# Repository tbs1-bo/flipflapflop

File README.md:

# flipflapflop
Steuerung einer Flipdot-Zielanzeige mit verschiedenen Mikrocontrollern.

Die Dokumentation befindet sich unter https://tbs1-bo.github.io/flipflapflop/

Die Demos lassen sich ganz ohne Installation direkt im Browser auf einer
virtuellen Flipdot-Anzeige ausprobieren:
https://tbs1-bo.github.io/flipflapflop/webdemo/ (Quelle: [webdemo/](webdemo/)).
  
Ein ähnliches Projekt zur Ansteuerung von LED-Anzeigen ist unter
[BoLED](https://github.com/tbs1-bo/BoLED) zu finden.

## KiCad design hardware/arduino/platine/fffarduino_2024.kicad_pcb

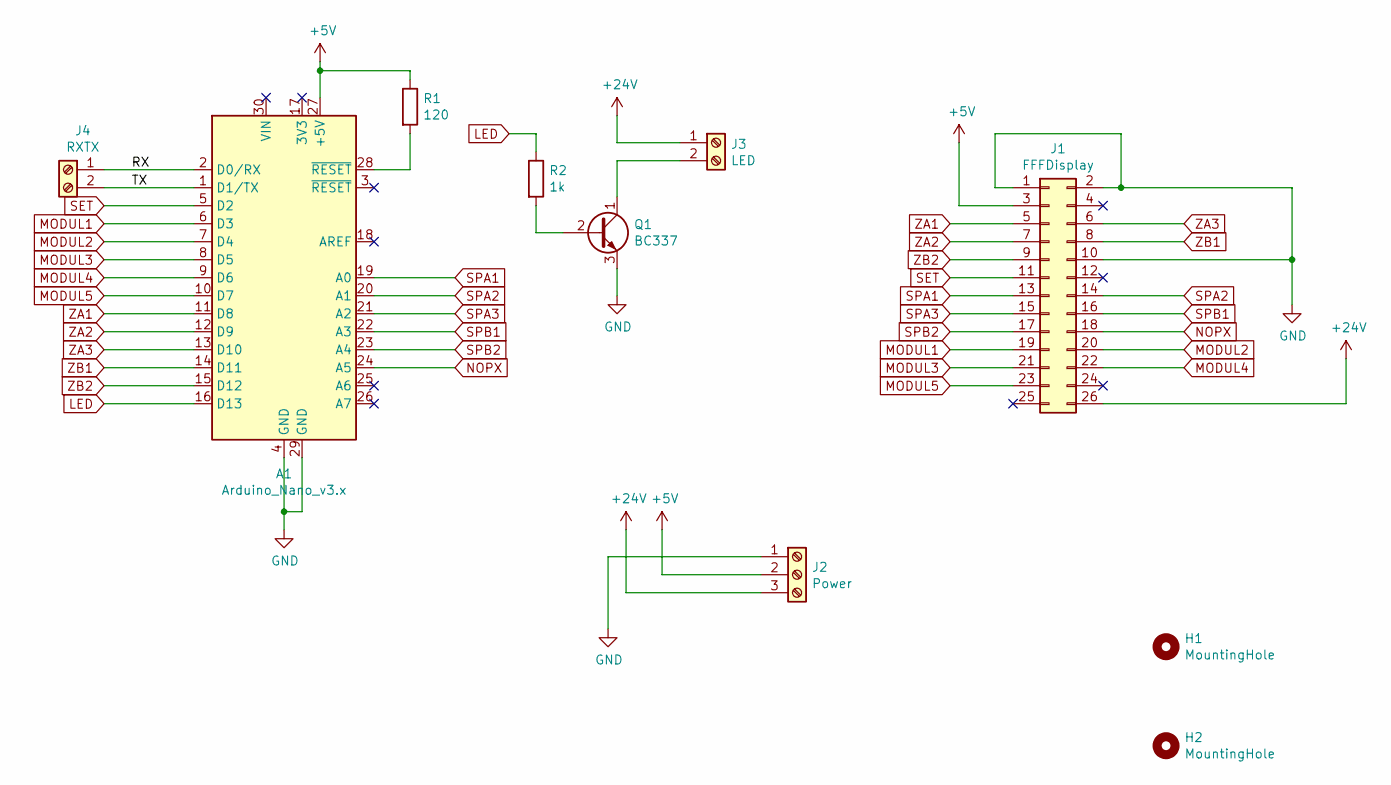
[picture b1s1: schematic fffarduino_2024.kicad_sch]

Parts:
A1: Arduino_Nano_v3.x; Arduino_Nano
H1: MountingHole; MountingHole_3.2mm_M3
H2: MountingHole; MountingHole_3mm
J1: FFFDisplay; PinHeader_2x13_P2.54mm_Horizontal
J2: Power; PhoenixContact_MSTBVA_2,5_3-G-5,08_1x03_P5.08mm_Vertical
J3: LED; PhoenixContact_MSTBVA_2,5_2-G-5,08_1x02_P5.08mm_Vertical
J4: RXTX; PinHeader_1x02_P2.54mm_Horizontal
Q1: BC337; TO-92_Wide
R1: 120; R_Axial_DIN0204_L3.6mm_D1.6mm_P2.54mm_Vertical
R2: 1k; R_Axial_DIN0207_L6.3mm_D2.5mm_P10.16mm_Horizontal

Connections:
+5V: A1.27 (+5V), J1.3, J2.2, R1.1
+24V: J1.26, J2.3, J3.1
/RX: A1.2 (D0/RX), J4.1
/TX: A1.1 (D1/TX), J4.2
GND: A1.4 (GND), A1.29 (GND), J1.1, J1.2, J1.10, J2.1, Q1.3 (E)
LED: A1.16 (D13), R2.1
MODUL1: A1.6 (D3), J1.19
MODUL2: A1.7 (D4), J1.20
MODUL3: A1.8 (D5), J1.21
MODUL4: A1.9 (D6), J1.22
MODUL5: A1.10 (D7), J1.23
NOPX: A1.24 (A5), J1.18
unnamed: A1.28 (~RESET), R1.2
unnamed: J3.2, Q1.1 (C)
unnamed: Q1.2 (B), R2.2
SET: A1.5 (D2), J1.11
SPA1: A1.19 (A0), J1.13
SPA2: A1.20 (A1), J1.14
SPA3: A1.21 (A2), J1.15
SPB1: A1.22 (A3), J1.16
SPB2: A1.23 (A4), J1.17
ZA1: A1.11 (D8), J1.5
ZA2: A1.12 (D9), J1.7
ZA3: A1.13 (D10), J1.6
ZB1: A1.14 (D11), J1.8
ZB2: A1.15 (D12), J1.9

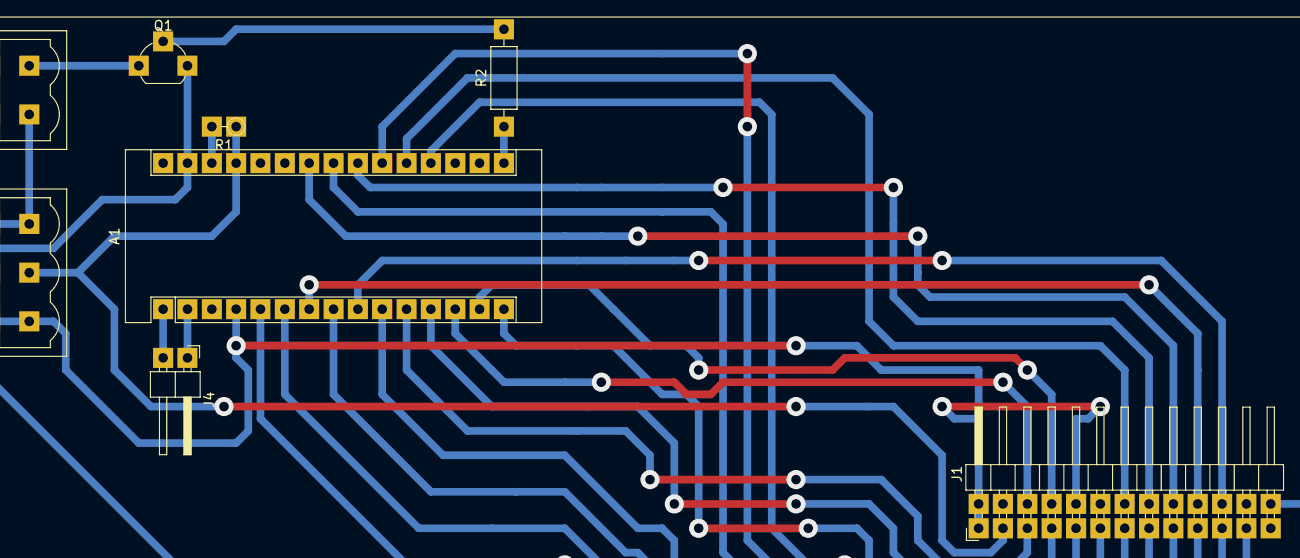
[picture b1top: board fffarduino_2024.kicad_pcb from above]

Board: 2 copper layers, 10 parts (0 on the bottom side), 26 nets.

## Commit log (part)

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2019-11-12 changed default topic name
2019-11-15 added make target for config file.
2020-05-09 gamejamdo
2020-05-09 gamejamdo
    gamejamdo
    gamejamdo
    gamejamdo
    gamejamdo
    gamejamdo
    gamejamdo
2020-05-09 lt19: removed special handling for ctf.
2020-05-10 typo
2020-05-11 gamejamdo: moved into module.
2020-05-11 formating
2020-05-11 making venv in parent.
2020-05-11 using release instead of git.
2020-05-11 removed ii.
2020-05-11 version configurable
2020-05-30 Beschreibung ergänzt.
2020-06-02 bf verlinkt
2020-07-24 doc: add link to handle auto reset.
2020-10-08 removed special handling for lt19
2020-10-08 index route removed
2020-10-08 parameter checking
2020-10-08 added test
2020-10-08 reordering imports
2020-10-08 formatting
2020-10-09 add: target for web
2020-10-09 added pygame requirement for arch
2020-10-09 added get_display
2020-10-09 whole image can be sent to display
    new route /page with
2020-10-09 second version for web interface.
    based on hug.
2020-10-10 added index page
2020-10-10 removed hug base web interface.
    in favor of flask.
2020-10-10 cofigurable webserver host.
2020-10-11 iframe of the video can be configured.
2020-10-12 display dimension shown
2020-10-12 add: test for plasma demo
2020-10-18 format
2020-10-18 GET route /page returns display content
2020-10-18 iframe in website replaced by link.
2020-10-18 removed small method set_buffer
2020-10-18 add 'x' for ignoring positions in page route
2020-10-18 removed unused import
2020-10-19 lni ressources
2020-10-19 add examples for the terminal.
2020-10-19 areas for the display
2020-10-19 added todo
2020-10-28 f strings removed
2020-10-28 add reverse_tunnel target
2020-10-28 added plasmademo remote test
2020-10-28 LNI20 startscreen
2020-10-28 aufgaben
2020-11-07 benchmarking the display
2020-11-13 minor change
2020-11-14 added feedback info.
2020-11-14 merges changes from branch lni_stat.
2020-11-14 lni20: demo
2021-10-11 gitlabci: add pip3 dependency
2022-10-30 adding pyproject file
2023-12-06 added flask
2023-12-06 font parameter no longer needed.
2023-12-06 added route to display text
2023-12-06 rm live image
2023-12-06 fetch use protocol
2023-12-06 request no longer form data
2023-12-06 rm unused
2023-12-21 pylint v3.0.3
2023-12-21 ignore cached files
2023-12-21 web doc
2023-12-21 add doc for webserver
2023-12-21 docs generated
2023-12-21 respect size in config
2023-12-21 add todo
2023-12-21 method show
2023-12-21 add support for animations
2023-12-21 lang set to en
2023-12-21 doc generated
2023-12-22 abort img seq if tool long
    incl. new config param
2023-12-22 showing txt customizable
2023-12-22 docgen
2023-12-22 switching to display api
2023-12-22 rm txt route
2023-12-22 rm old web conf url
2023-12-23 run tests
2023-12-23 add poetry
2023-12-23 rm venv
2023-12-23 migrate to poetry
2023-12-23 migrate to poetry 2
2023-12-23 rm requirements.txt
2023-12-23 zeroconf version
2023-12-24 add tests
2023-12-26 input validation
2023-12-26 test using random topic
2023-12-26 deploy update
2023-12-27 led support
2023-12-27 now using displayprovider
2023-12-27 added demo for binclock
2023-12-29 add line demo
2023-12-29 demo text scroller
2023-12-31 todos
2023-12-31 support of led
    maybe only dummy support for some display
2023-12-31 handle error in tests
2023-12-31 rm old doc
2023-12-31 rm old venv
2023-12-31 rm old todo
2023-12-31 added config for readthedocs
2023-12-31 rm todo rtf
    currently not supported. #8
2023-12-31 created issue
2023-12-31 red issue #10
2023-12-31 rm todo
    #9
2024-12-18 fix: demo
2024-12-18 code cleanup
2024-12-18 serial debug output
2024-12-21 use config for default values
2024-12-21 use display from display provider
2024-12-21 world for 38c3
2024-12-21 rogueflip debug output
2024-12-21 allow custom win message
2024-12-21 add joystick button handling and improve joystick detection output
2024-12-21 38c3 map file moved
2024-12-22 add assertion to ensure exactly one player is found on the map
2024-12-22 update coin collection method documentation for clarity
2024-12-22 refactor win condition handling into a separate method
2024-12-22 fix typos in comments and improve map loading output
2024-12-22 remove unused simulator and remote display functions from rogueflip.py
2024-12-22 add support for command line argument to specify world file
2024-12-22 disable fffmqtt.py in tests due to timeout issues with public mqtt test broker
2024-12-22 use daemon property instead of setDaemon method for thread in test_networking
    resolving deprecation warning.
2024-12-22 fix: correct formatting in tests.sh for fffmqtt.py exclusion
2024-12-22 add output messages in tests.sh
2024-12-22 update: update copyright year to 2025 in docgen configuration
2024-12-22 refactor: streamline main function by consolidating environment variable checks and display initialization
2024-12-22 add: create run script for rogueflip with environment variable setup
2024-12-22 rogueflip: log output in run script
2024-12-22 refactor: replace print statements with logging for better debugging
2024-12-22 fix: redirect stderr to log file for complete output capture in run script
2024-12-22 fix: adjust key event timing and extend input sequence in user event generator
2024-12-22 feat: add joystick support for FlappyDot controls and adjust input delay
2024-12-22 feat: track game duration and display elapsed time on game over
2024-12-22 feat: update FlappyDot controls to support joystick input
2024-12-23 feat: add new easy level for rogueflip game level
2024-12-23 doc joystick select button for game abort functionality
2024-12-23 fix: rename joystick select button to abort button for clarity
2024-12-24 fix: update configuration sample to include medium display dimensions
2024-12-24 fix: update image source path in rogueflip map file
2024-12-24 add debug print statement for display dimensions in get_display function
2024-12-24 debug msg
2024-12-24 fix: update win message display to handle newlines correctly
2024-12-24 font selection dependinig on display size
2024-12-24 38c3: big level file
2024-12-24 trying local running broker
2024-12-24 undo: remove fffmqtt.py from test scripts due to timeout issues
2024-12-24 main: mqtt broker to display
2024-12-24 MQTT display info publishing with JSON structure
2024-12-24 ranem
2024-12-24 38c3 run script mqtt
2024-12-24 Add menu functionality to the game with navigation and selection
2024-12-25 Refactor drawing logic in Game and World classes
2024-12-25 Rename handle_px method to __handle_px for improved encapsulation
2024-12-25 Rogueflip refactor update draw (#11)
    * first attempt
    * Refactor drawing logic in Game and World classes
    * Rename handle_px method to __handle_px for improved encapsulation
    ---------
2024-12-25 38c3: added labor logo
2024-12-25 Implement logging for MQTT connection and display operations
2024-12-25 Refactor extract input handling to method
2024-12-25 input handling: support both keyboard wasd and arrow keys
2024-12-27 runner updated
2024-12-28 rework demo base
2024-12-28 added
2024-12-29 cam2display
2024-12-29 opencv added
2024-12-29 using resized image
2024-12-30 add PyxelSim class for display simulation
2024-12-30 refactor cam2display to use App class and blur
2024-12-30 add Pyxel dependency to pyproject.toml
2024-12-30 added pyxel resources
2024-12-30 update get_display to include fps parameter for FlipDotSim
2024-12-30 update run_game.sh to use the correct world file for RogueFlip
2024-12-30 update rogueflip w orld
2024-12-30 add implementation option to simulator configuration
2024-12-30 implement close method and add test function for FlipDotSim
2024-12-30 initialize pygame and joystick support in FlappyDot demo
2024-12-30 add xvfb support for headless testing in CI workflow
2024-12-30 update CI workflow to install libsdl2-dev and remove xvfb dependency
2024-12-30 remove commented-out reset and set calls in test_flipdot_sim function
2024-12-30 change vis for run method
2024-12-30 update test_flipdot_sim dimensions for PyxelSim initialization
2024-12-30 add docstrings to PyxelSim class and methods
2024-12-30 add docstrings for close, test_flipdot_sim, and main functions
2024-12-30 add documentation for PyxelSim in simulator.rst
2024-12-31 mv default resource file
2024-12-31 set default resources and fps for PyxelSim initialization
2024-12-31 exclude test functions from documentation
2024-12-31 update firmware path in documentation for fffserial module
2024-12-31 fix formatting in Font class docstring problem in doc generation
2025-01-01 refactor App class to use a custom run method and adjust frame rate handling
2025-01-01 update font resource paths
2025-01-01 streamline test method
2025-01-01 source of fonts
2025-01-01 fix font test
2025-01-02 add port parameter to RemoteDisplay initialization in networking test
2025-01-02 add PixelflutServer class and test
2025-01-02 rename lt19.ipynb to ressources/lt19/lt19.ipynb
2025-01-02 add jupyterlab dependency to pyproject.toml
2025-01-02 lt19 notebook chdir
2025-01-02 move gamejamdo_2020-05 so subfolder
2025-01-07 doc: handle missing character encoding by returning space character
2025-01-07 character bitmap retrieval in Font class more readable
2025-01-07 doc: add docstring to letter method and update test_text_scroller function
2025-01-10 doc: add reference to additional content in Fediverse
2025-01-10 doc gen
2025-01-11 feat: add runtime parameter to run method for controlled execution duration
2025-01-11 test: add unit test for BinClock with runtime parameter
2025-01-11 add docstring to DemoSwitcher class
2025-01-11 docs: add notice about deprecated flipdotdisplay implementation using portexpander
2025-01-11 feat: add resource loading message to PyxelSim
2025-01-14 add deployment script for Raspberry Pi setup
2025-01-14 update service file to use Poetry for executing display server
2025-01-14 add testing notes for Raspberry Pi 3 Model B+
2025-01-14 fix: change apt install to apt-get install and adjust service file path
2025-01-15 feat: add startup message to display service with request timeout
2025-01-15 doc service script
2025-01-17 feat: add NONE fallback option to display provider
2025-01-17 feat: implement retry mechanism for display provider initialization
2025-01-17 fix: rename deployment script and optimize git clone command
2025-01-17 feat: add script for shallow cloning the repository
2025-01-17 feat: add nano to package installation in OpenWRT deployment script
2025-01-17 feat: add OpenWRT service script for display server initialization
2025-01-17 feat: copy service file and enable service in OpenWRT deployment script
2025-01-17 openwrt serivce fail cleanup
2025-01-17 feat: streamline OpenWRT deployment script by removing unnecessary git clone and adding file downloads
2025-01-17 feat: update OpenWRT deployment script to use file downloads instead of git clone
2025-01-17 feat: add respawn parameters to OpenWRT service script
2025-01-17 feat: update file download list in OpenWRT deployment script
2025-01-17 feat: add comments for firmware selector in OpenWRT deployment script
2025-01-17 feat: add DHCP client mode instructions to OpenWRT deployment script
2025-01-17 feat: reorder package installation commands in OpenWRT deployment script
2025-01-27 feat: add umdns package to OpenWRT deployment script
2025-01-27 feat: add alternative git checkout instructions to OpenWRT deployment script
2025-02-04 feat: add TODO for generalizing image display class in demos.py
2025-11-24 exit on error in deploy_rpi.sh
2025-12-20 c2display: add comment indicating creation during 38c3
2025-12-30 LED display configuration options
2025-12-30 Add MoireDemo class to demos.py
2025-12-30 file for text scrolling
2025-12-30 Adjust scrolling speed and update display method
2026-01-01 Add VirtualDisplay class to manage multiple smaller displays
2026-01-01 Enhance documentation for VirtualDisplay class with usage example
2026-01-01 Enhance docstring for _display_at method to clarify return values and behavior
2026-01-01 Enhance VirtualDisplay class with improved pixel handling and debugging output
2026-01-01 Enhance VirtualDisplay class documentation and update show method description
2026-01-01 updated docs
2026-01-01 class diagram updated
2026-01-01 fix tile underline
2026-01-02 rename print method to print_layout and enhance output with display details
2026-01-02 linking boled
